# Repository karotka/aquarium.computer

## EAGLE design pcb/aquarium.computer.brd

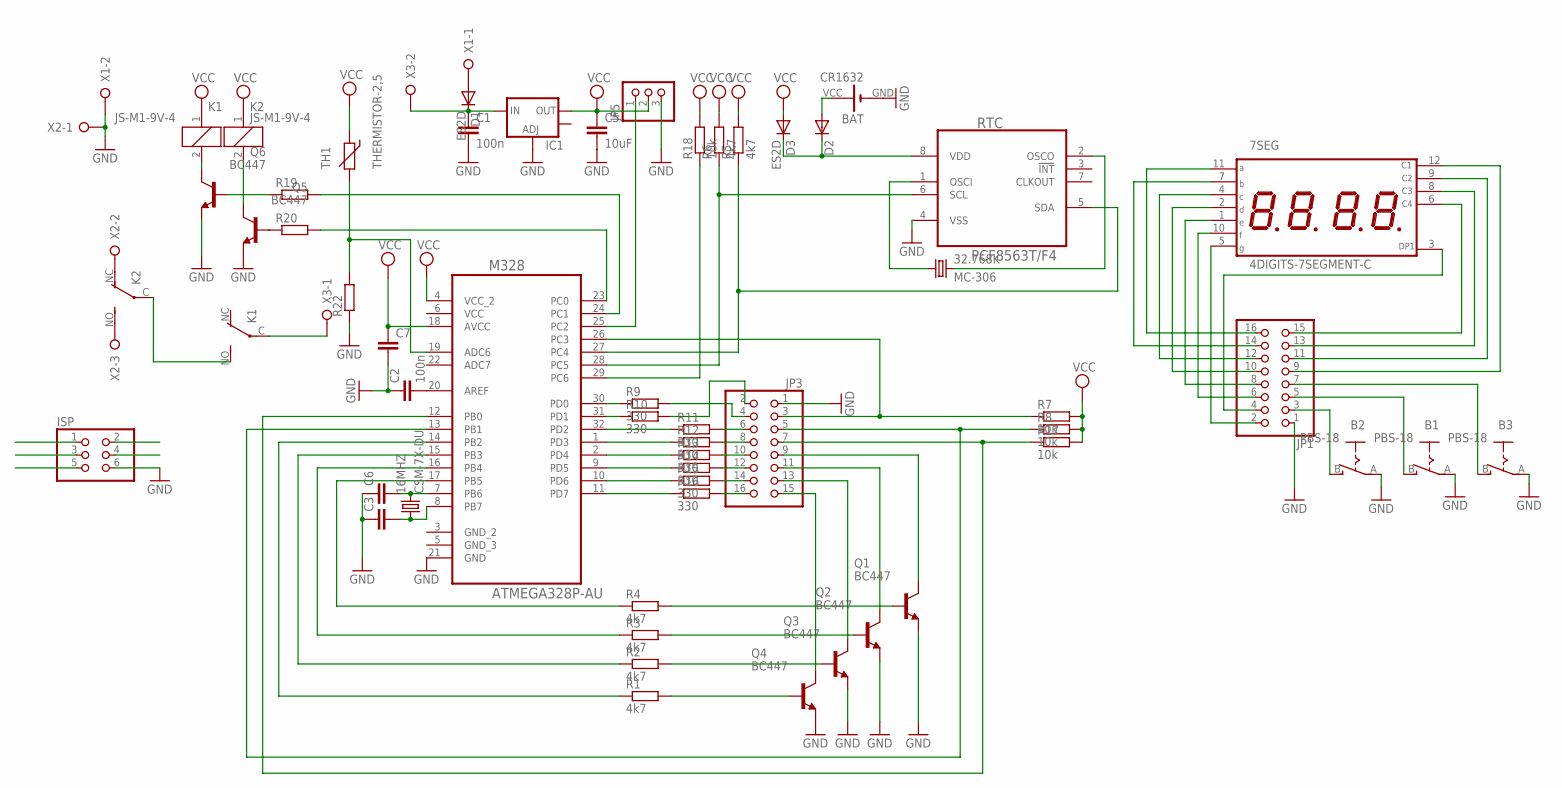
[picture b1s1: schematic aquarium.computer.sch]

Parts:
7SEG: 4DIGITS-7SEGMENT-C; CC56-12EWA
16MHZ: CSM-7X-DU
32.768K: MC-306
B1, B2, B3: PBS-18; PBS18
BAT: CR1632; CR3232
C1: 100n; C025-040X050
C2: 100n; C1206
C3, C6: C-EUC0805K; C0805K
C5: 10uF; C025-050X050
C7: C-EU025-040X050; C025-040X050
D1, D3: ES2D; SMB
D2: DIODE-SOD80C; SOD80C
IC1: V_REG_LM1117SOT223; SOT223
ISP: PINHD-2X3; 2X03
JP1, JP3: PINHD-2X8; 2X08
JP5: PINHD-1X3; 1X03
K1, K2: JS-M1-9V-4; JS-M
M328: ATMEGA328P-AU; QFP80P900X900X120-32N
Q1, Q2, Q3, Q4, Q5, Q6: BC447; TO92-EBC
R1, R2, R3, R4: 4k7; 0207/10
R5, R6: 4k7; R1206
R7, R8, R17, R18: 10k; 0207/10
R9, R10, R11, R12, R13, R14, R15, R16: 330; 0207/10
R19, R20: R-EU_0207/10; 0207/10
R22: R-EU_R1206; R1206
RTC: PCF8563T/F4; SOIC127P600X175-8N
TH1: THERMISTOR-2,5; RS-2,5
X1, X3: W237-02P; W237-132
X2: W237-3E

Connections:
GND: B1.A, B2.A, B3.A, BAT.GND (-), C1.2, C2.1, C3.1, C5.2, C6.1, C7.2, IC1.1 (ADJ), ISP.6, JP1.1, JP3.1, JP5.3, M328.21 (GND), Q1.E, Q2.E, Q3.E, Q4.E, Q5.E, Q6.E, R22.1, RTC.4 (VSS), X1.2, X2.1
MISO: ISP.1, M328.16 (PB4), R3.1
MOSI: ISP.4, M328.15 (PB3), R2.1
unnamed: M328.28 (PC5), R6.1, RTC.6 (SCL)
unnamed: M328.27 (PC4), R5.1, RTC.5 (SDA)
unnamed: Q5.B, R20.1
unnamed: Q1.B, R4.2
unnamed: Q2.B, R3.2
unnamed: Q3.B, R2.2
unnamed: M328.31 (PD1), R10.1
unnamed: M328.32 (PD2), R11.1
unnamed: M328.1 (PD3), R12.1
unnamed: M328.2 (PD4), R13.1
unnamed: M328.9 (PD5), R14.1
unnamed: K1.C, X3.1
unnamed: M328.10 (PD6), R15.1
unnamed: M328.11 (PD7), R16.1
unnamed: JP3.7, M328.12 (PB0), R17.1
unnamed: M328.14 (PB2), R1.1
unnamed: JP3.2, R10.2
unnamed: 32.768K.1, RTC.1 (OSCI)
unnamed: 32.768K.4 (2), RTC.2 (OSCO)
unnamed: JP3.4, R9.2
unnamed: JP3.6, R11.2
unnamed: JP3.8, R12.2
unnamed: JP3.10, R13.2
unnamed: JP3.12, R14.2
unnamed: JP3.14, R15.2
unnamed: JP3.16, R16.2
unnamed: Q4.B, R1.2
unnamed: M328.30 (PD0), R9.1
unnamed: 16MHZ.2, C6.2, M328.7 (PB6)
unnamed: 16MHZ.1, C3.2, M328.8 (PB7)
unnamed: 7SEG.11 (A), JP1.16
unnamed: M328.23 (PC0), R20.2
unnamed: M328.24 (PC1), R19.2
unnamed: JP3.3, M328.26 (PC3), R7.1
unnamed: M328.19 (ADC6), R22.2, TH1.2
unnamed: JP3.5, M328.13 (PB1), R8.1
unnamed: JP3.11, Q2.C
unnamed: JP3.9, Q1.C
unnamed: K2.2, Q5.C
unnamed: K1.2, Q6.C
unnamed: K1.NO (S), K2.C
unnamed: BAT.VCC (+), D2.A
unnamed: 7SEG.7 (B), JP1.14
unnamed: K2.NC (O), X2.2
unnamed: K2.NO (S), X2.3
unnamed: Q6.B, R19.1
unnamed: B2.B (S), JP1.3
unnamed: B1.B (S), JP1.5
unnamed: B3.B (S), JP1.7
unnamed: 7SEG.10 (F), JP1.6
unnamed: 7SEG.4 (C), JP1.12
unnamed: 7SEG.2 (D), JP1.10
unnamed: 7SEG.1 (E), JP1.8
unnamed: 7SEG.5 (G), JP1.2
unnamed: 7SEG.6 (C4), JP1.15
unnamed: 7SEG.12 (C1), JP1.9
unnamed: 7SEG.9 (C2), JP1.11
unnamed: 7SEG.8 (C3), JP1.13
unnamed: 7SEG.3 (DP1), JP1.4
unnamed: JP3.15, Q4.C
unnamed: JP3.13, Q3.C
unnamed: C2.2, M328.20 (AREF)
unnamed: D2.C, D3.C, RTC.8 (VDD)
unnamed: JP5.1, M328.25 (PC2)
unnamed: C1.1, D1.C, IC1.3 (IN), X3.2
unnamed: D1.A, X1.1
RESET: ISP.5, M328.29 (PC6), R18.1
SCK: ISP.3, M328.17 (PB5), R4.1
VCC: C5.1, C7.1, D3.A, IC1.2 (OUT), ISP.2, JP5.2, K1.1, K2.1, M328.4 (VCC_2), M328.6 (VCC), M328.18 (AVCC), R5.2, R6.2, R7.2, R8.2, R17.2, R18.2, TH1.1

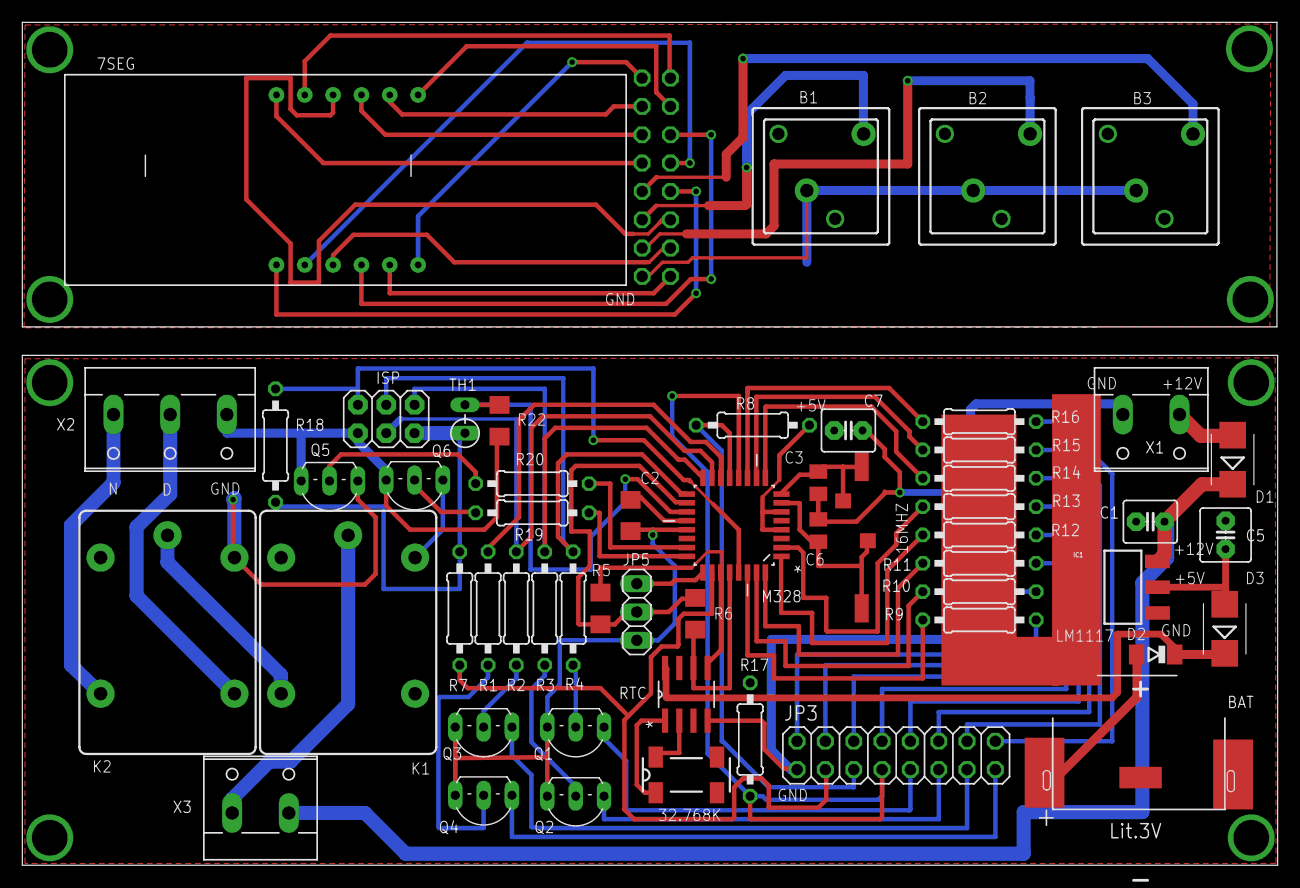
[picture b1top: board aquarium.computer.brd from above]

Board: 2 copper layers, 112.5 x 75.6 mm, 56 parts (1 on the bottom side), 72 nets.

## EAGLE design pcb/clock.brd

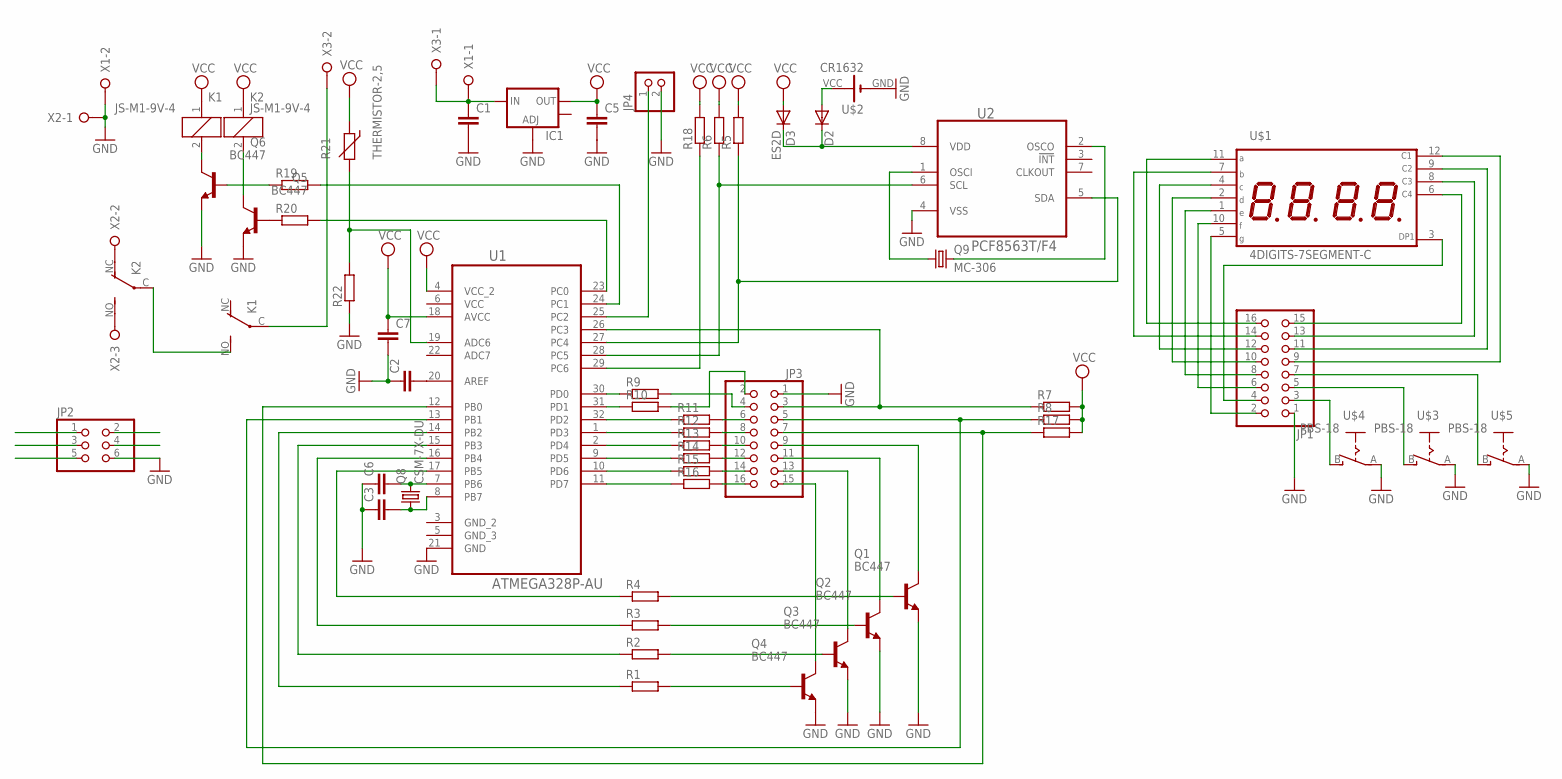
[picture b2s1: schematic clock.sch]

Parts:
C1, C7: C-EU025-040X050; C025-040X050
C2: C-EUC1206; C1206
C3, C6: C-EUC0805K; C0805K
C5: C-EU025-050X050; C025-050X050
D2: DIODE-SOD80C; SOD80C
D3: ES2D; SMB
IC1: V_REG_LM1117SOT223; SOT223
JP1, JP3: PINHD-2X8; 2X08
JP2: PINHD-2X3; 2X03
JP4: PINHD-1X2; 1X02
K1, K2: JS-M1-9V-4; JS-M
Q1, Q2, Q3, Q4, Q5, Q6: BC447; TO92-EBC
Q8: CSM-7X-DU
Q9: MC-306
R1, R2, R3, R4, R7, R8, R9, R10, R11, R12, R13, R14, R15, R16, R17, R18, R19, R20: R-EU_0207/10; 0207/10
R5, R6, R22: R-EU_R1206; R1206
R21: THERMISTOR-2,5; RS-2,5
U1: ATMEGA328P-AU; QFP80P900X900X120-32N
U2: PCF8563T/F4; SOIC127P600X175-8N
U$1: 4DIGITS-7SEGMENT-C; CC56-12EWA
U$2: CR1632; CR3232
U$3, U$4, U$5: PBS-18; PBS18
X1, X3: W237-02P; W237-132
X2: W237-3E

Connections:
GND: C1.2, C2.1, C3.1, C5.2, C6.1, C7.2, IC1.1 (ADJ), JP1.1, JP2.6, JP3.1, JP4.2, Q1.E, Q2.E, Q3.E, Q4.E, Q5.E, Q6.E, R22.1, U1.21 (GND), U2.4 (VSS), U$2.GND (-), U$3.A, U$4.A, U$5.A, X1.2, X2.1
MISO: JP2.1, R3.1, U1.16 (PB4)
MOSI: JP2.4, R2.1, U1.15 (PB3)
unnamed: R6.1, U1.28 (PC5), U2.6 (SCL)
unnamed: R5.1, U1.27 (PC4), U2.5 (SDA)
unnamed: Q5.B, R20.1
unnamed: Q1.B, R4.2
unnamed: Q2.B, R3.2
unnamed: Q3.B, R2.2
unnamed: R10.1, U1.31 (PD1)
unnamed: R11.1, U1.32 (PD2)
unnamed: R12.1, U1.1 (PD3)
unnamed: R13.1, U1.2 (PD4)
unnamed: R14.1, U1.9 (PD5)
unnamed: K1.C, X3.2
unnamed: R15.1, U1.10 (PD6)
unnamed: R16.1, U1.11 (PD7)
unnamed: JP3.7, R17.1, U1.12 (PB0)
unnamed: R1.1, U1.14 (PB2)
unnamed: JP3.2, R10.2
unnamed: Q9.1, U2.1 (OSCI)
unnamed: Q9.4 (2), U2.2 (OSCO)
unnamed: JP3.4, R9.2
unnamed: JP3.6, R11.2
unnamed: JP3.8, R12.2
unnamed: JP3.10, R13.2
unnamed: JP3.12, R14.2
unnamed: JP3.14, R15.2
unnamed: JP3.16, R16.2
unnamed: Q4.B, R1.2
unnamed: R9.1, U1.30 (PD0)
unnamed: C6.2, Q8.2, U1.7 (PB6)
unnamed: C3.2, Q8.1, U1.8 (PB7)
unnamed: JP1.16, U$1.11 (A)
unnamed: R20.2, U1.23 (PC0)
unnamed: R19.2, U1.24 (PC1)
unnamed: JP3.3, R7.1, U1.26 (PC3)
unnamed: R21.2, R22.2, U1.19 (ADC6)
unnamed: JP3.5, R8.1, U1.13 (PB1)
unnamed: JP3.11, Q2.C
unnamed: JP3.9, Q1.C
unnamed: K2.2, Q5.C
unnamed: K1.2, Q6.C
unnamed: K1.NO (S), K2.C
unnamed: D2.A, U$2.VCC (+)
unnamed: JP1.14, U$1.7 (B)
unnamed: K2.NC (O), X2.2
unnamed: K2.NO (S), X2.3
unnamed: Q6.B, R19.1
unnamed: JP1.3, U$4.B (S)
unnamed: JP1.5, U$3.B (S)
unnamed: JP1.7, U$5.B (S)
unnamed: JP1.6, U$1.10 (F)
unnamed: JP1.12, U$1.4 (C)
unnamed: JP1.10, U$1.2 (D)
unnamed: JP1.8, U$1.1 (E)
unnamed: JP1.2, U$1.5 (G)
unnamed: JP1.15, U$1.6 (C4)
unnamed: JP1.9, U$1.12 (C1)
unnamed: JP1.11, U$1.9 (C2)
unnamed: JP1.13, U$1.8 (C3)
unnamed: JP1.4, U$1.3 (DP1)
unnamed: JP3.15, Q4.C
unnamed: JP3.13, Q3.C
unnamed: C2.2, U1.20 (AREF)
unnamed: D2.C, D3.C, U2.8 (VDD)
unnamed: JP4.1, U1.25 (PC2)
unnamed: C1.1, IC1.3 (IN), X1.1, X3.1
RESET: JP2.5, R18.1, U1.29 (PC6)
SCK: JP2.3, R4.1, U1.17 (PB5)
VCC: C5.1, C7.1, D3.A, IC1.2 (OUT), JP2.2, K1.1, K2.1, R5.2, R6.2, R7.2, R8.2, R17.2, R18.2, R21.1, U1.4 (VCC_2), U1.6 (VCC), U1.18 (AVCC)

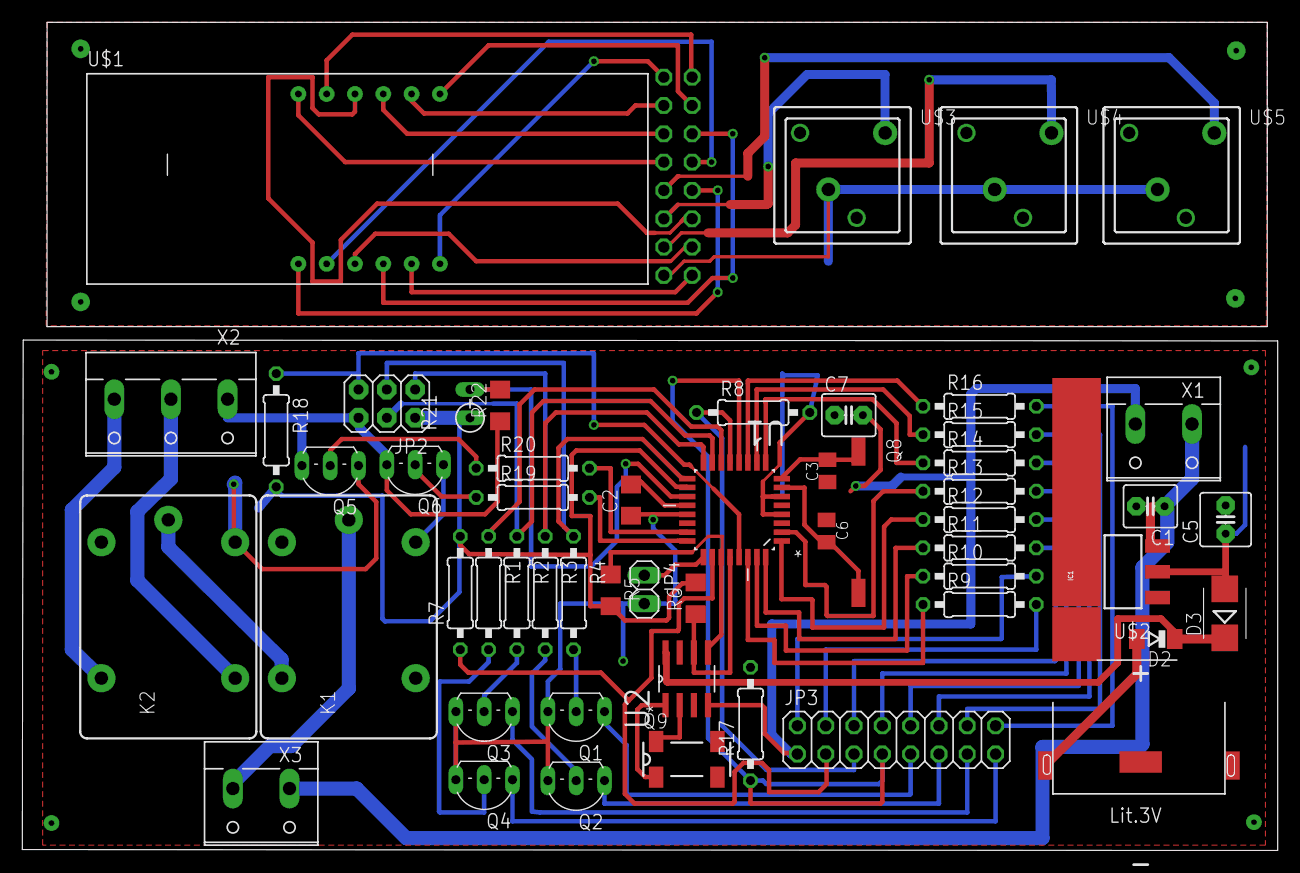
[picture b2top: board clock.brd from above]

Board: 2 copper layers, 112.6 x 74.3 mm, 55 parts (1 on the bottom side), 71 nets.

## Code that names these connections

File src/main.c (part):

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    getTime();

    while(1) {
        // if set is set for modify values PB1
        if (debounce(&PINB, PB1)) {
            changeStateCounter = 0;

            if (set) {
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            }
        }

        // button for change position for update PC3
        if (debounce(&PINC, PC3)) {
            changeStateCounter = 0;

            switch (show) {
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            }
        }

        if (debounce(&PINB, PB0)) {
            changeStateCounter = 0;
            show = show_switch;
            switchStatus++;
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
        // lights
        if (daySt == d_day) { // day
            PORTC |= (1 << PC1);
            PORTC |= (1 << PC0);
        } else if (daySt == d_night) { // night
            PORTC |= (1 << PC1);
            PORTC &= ~(1 << PC0);
        } else { // off
            PORTC &= ~(1 << PC1);
            PORTC &= ~(1 << PC0);
        }

        // CO2
        int co2on  = (co2[0] * 60) + co2[1];
        int co2off = (co2[2] * 60) + co2[3];
        if (co2on <= t && t < co2off) {
            PORTC |= (1 << PC2);
        } else {
            PORTC &= ~(1 << PC2);
        }
    }

    if (switchStatus == switch_off) {
        PORTC &= ~(1 << PC1);
        PORTC &= ~(1 << PC0);
    }
    if (switchStatus == switch_night) {
        PORTC |= (1 << PC1);
        PORTC &= ~(1 << PC0);
    }
    if (switchStatus == switch_day) {
        PORTC |= (1 << PC1);
        PORTC |= (1 << PC0);
    }

    // automaticaly swith to show time and
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        break;
    }

    PORTB &= ~(1 << PB2);//0
    PORTB &= ~(1 << PB3);//1
    PORTB &= ~(1 << PB4);//2
    PORTB &= ~(1 << PB5);//3

    blickCounter++;

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
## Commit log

2014-07-28 add files first commit
2014-07-29 programming date and time
2014-07-30 add programable time for switching
2014-07-30 add rtc library
2014-07-31 optimalization
2014-07-31 next optimalization and base function done
2014-07-31 automaticly swith to show time and back to show date
2014-08-01 timer switch optimalization
2014-08-01 add switch timer
2014-08-02 board first commit
2014-08-03 some small things
2014-08-03 add adc
2014-08-03 rm adc.o :)
2014-08-03 temperature measurment
2014-08-04 finishing pcb
2014-08-06 some changes problem with set time
2014-08-08 add 3 button
2014-08-08 extend board
2014-08-10 add thermistor code
2014-08-10 add only char print
2014-08-11 reverse char
2014-08-12 timer switch on
2014-08-17 temp stable version
2014-08-17 only char print stable version
2014-08-17 my thermistor settings
2014-08-18 board modification for use external device, move thermistor to adc6, software is not modificated yet
2014-08-20 rename
2015-09-04 thermistor code
2015-10-05 remove fifo

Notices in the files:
parts and their libraries:
sparkfun: Licensing: CC v3.0 Share-Alike You are welcome to use this library for commercial purposes.
